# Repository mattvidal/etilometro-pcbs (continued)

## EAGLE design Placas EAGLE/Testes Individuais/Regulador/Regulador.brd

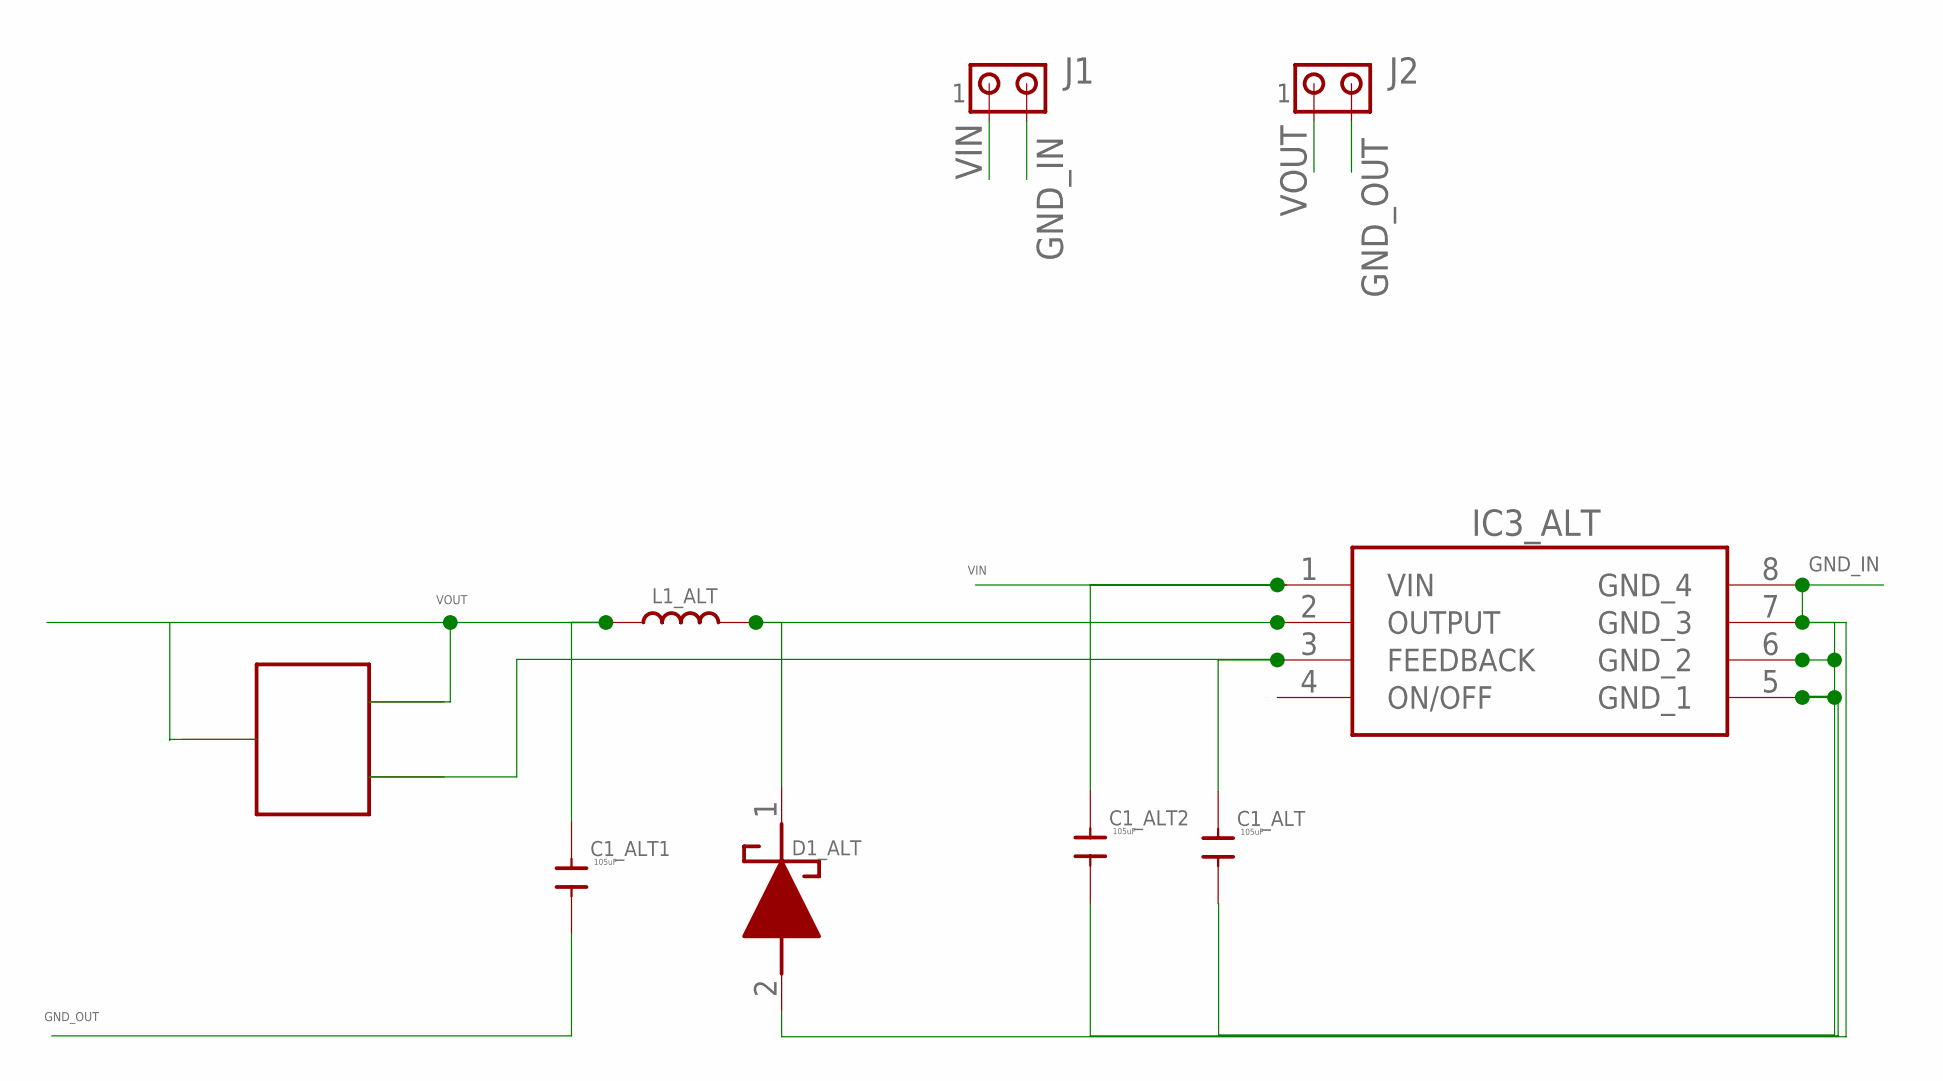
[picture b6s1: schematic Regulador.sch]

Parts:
C1_ALT, C1_ALT1, C1_ALT2: 105uF; C0805
D1_ALT: 1N5819HW1-7-F; SODFL3518X115N
IC3_ALT: XL1509-3.3E1; SOIC127P600X175-8N
J1, J2: MTA02-156; 1X2MTA
L1_ALT: 47uH; PIO73
U$1: TRIMPOT

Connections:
GND_IN: C1_ALT.1, C1_ALT2.1, D1_ALT.2 (A), IC3_ALT.5 (GND_1), IC3_ALT.6 (GND_2), IC3_ALT.7 (GND_3), IC3_ALT.8 (GND_4), J1.2
GND_OUT: C1_ALT1.1, J2.2
unnamed: D1_ALT.1 (K), IC3_ALT.2 (OUTPUT), L1_ALT.1
unnamed: C1_ALT.2, IC3_ALT.3 (FEEDBACK), U$1.OUT
VIN: C1_ALT2.2, IC3_ALT.1 (VIN), J1.1
VOUT: C1_ALT1.2, J2.1, L1_ALT.2, U$1.VCC1, U$1.VCC2

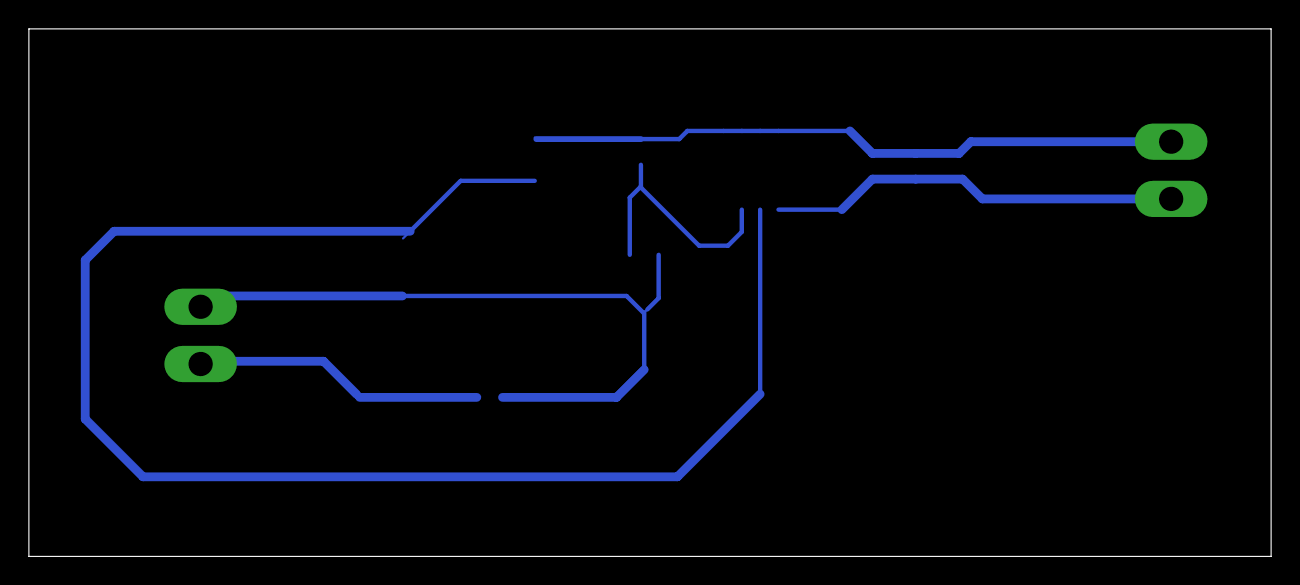
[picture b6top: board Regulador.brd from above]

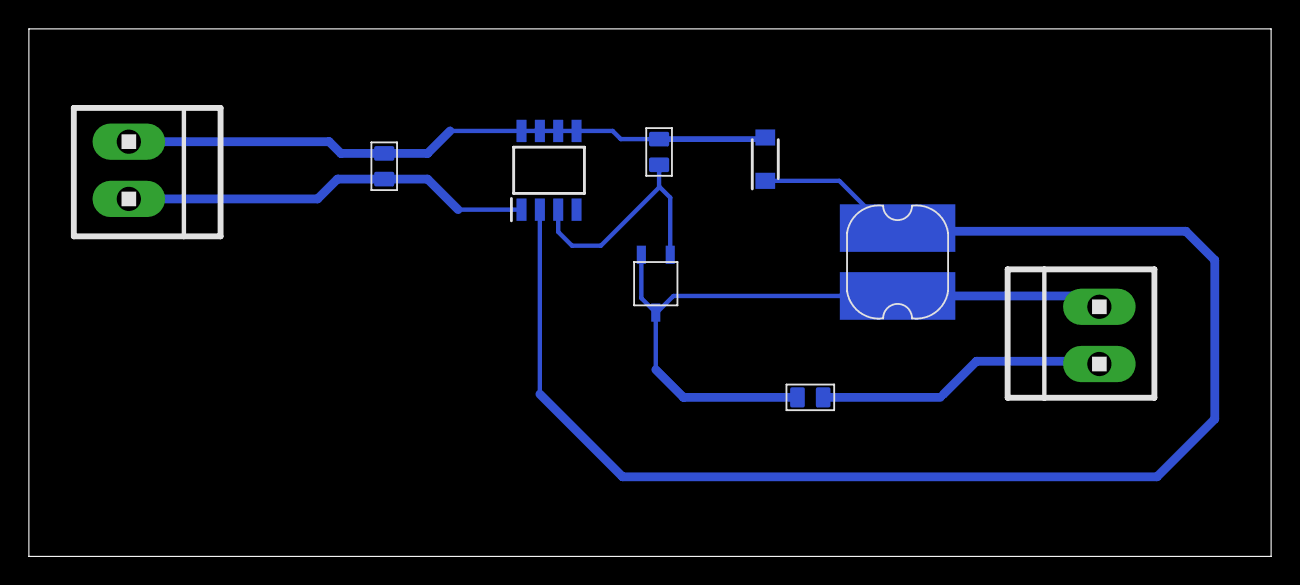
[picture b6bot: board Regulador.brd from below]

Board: 2 copper layers, 86.0 x 36.5 mm, 9 parts (9 on the bottom side), 6 nets.
